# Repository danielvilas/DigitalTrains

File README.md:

# DigitalTrains
Digital Trains is a repository for storing and sharing my DCC/LCC setups

Up to Date this contians Circuits, boards and projects usefull for my model layout.
Each folder is a project I started. some are finished, others are Work In Progress

|Folder| Description|Status[^1]|
|:--|:--|:--|
|[ArduinoDCC++](ArduinoDCC++)|Board for use whit DCC++|Deprecated for DccBlocks
|[Breaker](Breaker)|DC breaker board, shorts protections|Frozen, no need on DCC[^2]|
|[dcc-turnout](dcc-turnout)|Board to control a turnout with servo| Alive - prototype phase|
|[dcc-turnout-config](dcc-turnout-config)|Tool to configure the dcc-turnout boards| Alive - conceptual design|
|[DccBlocks](DccBlocks)| Components to create a DCC system whit DCC++. Has subprojects| Stall - currently works, needs update to DCC++EX|
|[docs](docs)| Different documents may be usefull| Alive - Slow|
|[Esp32Lcc](Esp32Lcc)| Use an ESP32 as node for LCC| Stall - Reading about|
|[Interfaces](Interfaces)| Reference Designs to add conectivity| Done - until new needs|
|[kibot](kibot)| Yaml Config for kibot scripts..| Done - until new needs|
|[Libs](Libs)| KiCad Libraries| WIP |
|[MimicPanel](MimicPanel)| Hardware and software to create Mimic Panels| WIP|
|[pcbdraw](pcbdraw)| PcbDraw Library| WIP|
|[STM32103_Devel](STM32103_Devel)|STM32F103 Custom board| Depecated for refenece repository|

[^1]: More info inside each project
[^2]: Let the central handle shorts :sunglasses:

## Versioning
First projects uses a folder per version system, easy to follow, easy to view older versions, but mess the file system.

Current system based on tags, and the creation of doc directories with PDFs of the schematic and the layers.
## Tags of projects
* __db_dt_VERSION__ -> DccBlocks/Detection
* __dt_VERSION__ -> DccTurnout
* __dt_ms_VERSION__ -> DccTurnout/Modules/ServoPmosModule
* __db_abc_stop_VERSION__ -> DccBlocks/ABC/AbcStop
* __db_pd_VERSION__ ->  DccBlocks/DccPowerDistribution
* __i_lb_esp32_VERSION__ -> Interfaces/LocoBufferEsp32/board/LocoBufferEsp32
* __i_lb_esp32_c_VERSION__ -> Interfaces/LocoBufferEsp32/board/LocoBufferEsp32Craddle

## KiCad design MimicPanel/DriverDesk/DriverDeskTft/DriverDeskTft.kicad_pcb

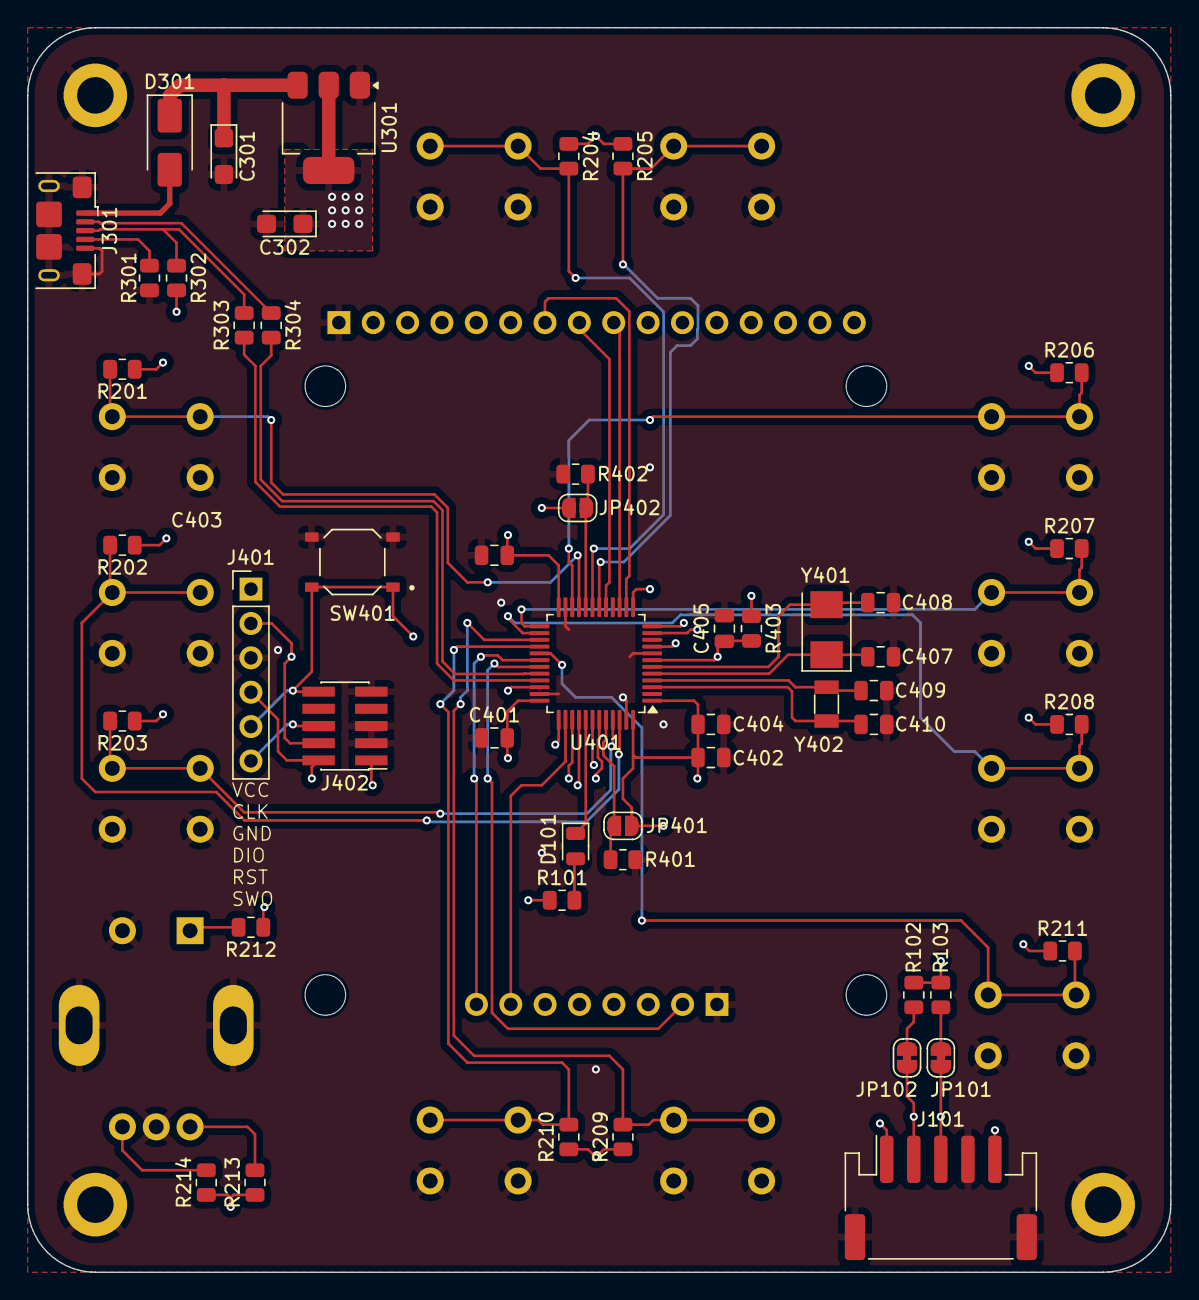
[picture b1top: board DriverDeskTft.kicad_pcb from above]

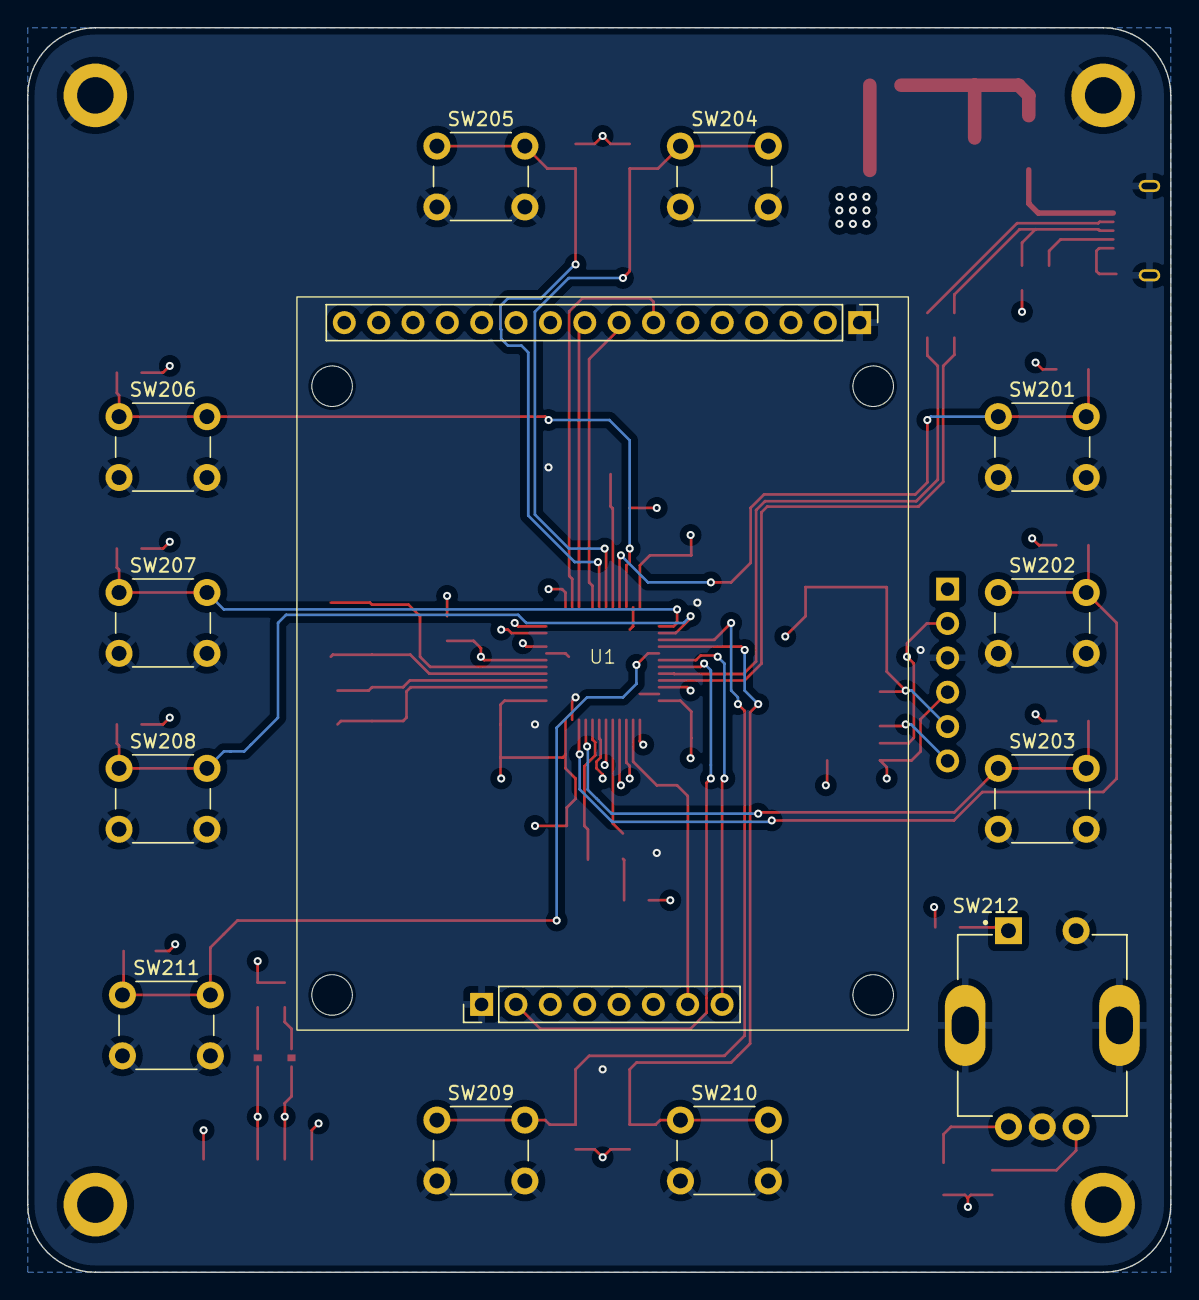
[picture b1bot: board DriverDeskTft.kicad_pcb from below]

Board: 4 copper layers, 84.5 x 92.0 mm, 67 parts (13 on the bottom side), 46 nets.

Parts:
C301, C302: 10uF; CP_EIA-3216-18_Kemet-A
C401, C402, C403, C404, C405: 100nf; C_0805_2012Metric
C407, C408: 20pf; C_0805_2012Metric
C409, C410: 10pf; C_0805_2012Metric
D101: LED; LED_0805_2012Metric
D301: ss14; D_SMA
H1, H2, H3, H4: MountingHole_Pad; MountingHole_2.7mm_M2.5_DIN965_Pad
J101: S5B-PH-SM4-TB; JST_PH_S5B-PH-SM4-TB_1x05-1MP_P2.00mm_Horizontal
J301: USB_B_Micro; USB_Micro-B_Amphenol_10118193-0001LF_Horizontal
J401: Conn_01x06_P1.27; PinHeader_1x06_P2.54mm_Vertical
J402: Conn_02x05 Odd_Even; PinHeader_2x05_P1.27mm_Vertical_SMD
JP101, JP102: SolderJumper_2_Bridged; SolderJumper-2_P1.3mm_Bridged_RoundedPad1.0x1.5mm
JP401, JP402: SolderJumper_2_Open; SolderJumper-2_P1.3mm_Open_RoundedPad1.0x1.5mm
R101: 1K; R_0805_2012Metric
R102, R103, R201, R202, R203, R204, R205, R206, R207, R208, R209, R210, R211, R212, R213, R214, R401, R402, R403: 10K; R_0805_2012Metric
R301: 100K; R_0805_2012Metric
R302: 1K5; R_0805_2012Metric
R303, R304: 20; R_0805_2012Metric
SW201, SW202, SW203, SW204, SW205, SW206, SW207, SW208, SW209, SW210, SW211: SW_Push; SW_PUSH_6mm_H5mm
SW212: RotaryEncoder_Switch; XDCR_PEC11R-4215F-S0024
SW401: PTS526; SW_PTS526_SM08_SMTR2_LFS
U1: TFT 1.8 SPI
U301: AMS1117-3.3; SOT-223-3_TabPin2
U401: STM32F103CBTx; LQFP-48_7x7mm_P0.5mm
Y401: 8MHz; Crystal_SMD_5032-2Pin_5.0x3.2mm
Y402: 32.768kHz; Crystal_SMD_3215-2Pin_3.2x1.5mm

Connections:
+5V: C301.1, D301.1 (K), U301.3 (VI)
/BTN_1: R201.2, SW201.1, U401.21 (PB10)
/BTN_2: R202.2, SW202.1, U401.46 (PB9)
/BTN_3: R203.2, SW203.1, U401.45 (PB8)
/BTN_4: R204.2, SW204.1, U401.19 (PB1)
/BTN_5: R205.2, SW205.1, U401.18 (PB0)
/BTN_6: R206.2, SW206.1, U401.22 (PB11)
/BTN_7: R207.2, SW207.1, U401.25 (PB12)
/BTN_8: R208.2, SW208.1, U401.26 (PB13)
/BTN_9: R209.2, SW209.1, U401.27 (PB14)
/BTN_10: R210.2, SW210.1, U401.28 (PB15)
/I2C_INT: J101.5, U401.40 (PB4)
/I2C_SCL: J101.3, JP101.1 (A), U401.42 (PB6)
/I2C_SDA: J101.2, JP102.1 (A), U401.43 (PB7)
/LED: D101.1 (K), U401.41 (PB5)
/RENC_A: R213.2, SW212.A, U401.11 (PA1)
/RENC_B: R214.2, SW212.B, U401.12 (PA2)
/RENC_H: R211.2, SW211.1, U401.29 (PA8)
/RENC_S: R212.2, SW212.S1, U401.13 (PA3)
/STM32F103/BOOT0: JP401.1 (A), R401.1, U401.44 (BOOT0)
/STM32F103/BOOT1: JP402.1 (A), R402.1, U401.20 (PB2)
/STM32F103/NRST: C405.1, J401.5, J402.10, R403.2, SW401.1, U401.7 (NRST)
/STM32F103/OSC32_IN: C409.1, U401.4 (PC15), Y402.1
/STM32F103/OSC32_OUT: C410.1, U401.3 (PC14), Y402.2
/STM32F103/OSC_IN: C407.1, U401.5 (PD0), Y401.1
/STM32F103/OSC_OUT: C408.1, U401.6 (PD1), Y401.2
/STM32F103/PA13: J401.4, J402.2, U401.34 (PA13)
/STM32F103/PA14: J401.2, J402.4, U401.37 (PA14)
/STM32F103/PB3: J401.6, J402.6, U401.39 (PB3)
/TFT_BL: U1.18 (BL), U401.31 (PA10)
/TFT_CLK: U1.9 (SCL), U401.15 (PA5)
/TFT_CS: U1.23 (CS), U401.38 (PA15)
/TFT_DC: U1.7 (RS), U401.14 (PA4)
/TFT_DIN: U1.8 (SDA), U401.17 (PA7)
/TFT_RST: U1.24 (RST), U401.30 (PA9)
/USB/USB_N: J301.2 (D-), R304.1
/USB/USB_P: J301.3 (D+), R302.1, R303.2
/USB/VCC_USB: D301.2 (A), J301.1 (VBUS)
/USB_DN: R304.2, U401.32 (PA11)
/USB_DP: R303.1, U401.33 (PA12)
GND: C301.2, C302.2, C401.1, C402.1, C403.1, C404.1, C405.2, C407.2, C408.2, C409.2, C410.2, H1.1, H2.1, H3.1, H4.1, J101.4, J101.MP (MountPin), J301.5 (GND), J301.6 (Shield), J401.3, J402.3, J402.5, J402.9, R301.2, R401.2, R402.2, SW201.2, SW202.2, SW203.2, SW204.2, SW205.2, SW206.2, SW207.2, SW208.2, SW209.2, SW210.2, SW211.2, SW212.C, SW212.MP, SW212.S2, SW401.2, U1.1 (GND), U1.17 (GND), U301.1 (GND), U401.8 (VSSA), U401.23 (VSS), U401.35 (VSS), U401.47 (VSS)
unnamed: D101.2 (A), R101.2
unnamed: J301.4 (ID), R301.1
unnamed: JP101.2 (B), R103.2
unnamed: JP102.2 (B), R102.2
VCC: C302.1, C401.2, C402.2, C403.2, C404.2, J101.1, J401.1, J402.1, JP401.2 (B), JP402.2 (B), R101.1, R102.1, R103.1, R201.1, R202.1, R203.1, R204.1, R205.1, R206.1, R207.1, R208.1, R209.1, R210.1, R211.1, R212.1, R213.1, R214.1, R302.2, R403.1, U1.2 (VCC), U1.19 (VCC), U301.2 (VO), U401.1 (VBAT), U401.9 (VDDA), U401.24 (VDD), U401.36 (VDD), U401.48 (VDD)

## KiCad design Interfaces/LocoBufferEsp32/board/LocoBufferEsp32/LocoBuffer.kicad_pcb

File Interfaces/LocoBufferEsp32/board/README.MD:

# LocoBuffer from LocoLinx32U4

Board for use wiht the [https://github.com/mrrwa/LocoNet/tree/master/examples/LocoLinx32U4] code, there is a copy on this repository for platform.io .

# 0.0.1
- [x] USB
- [x] Loconet
- [x] Leds loconet
- [x] ESP32
- [ ] Btn Reset

# 0.0.X
- [] Loconet Power 
- [] Loconet Master
- [] USB-C
- [] Non-Inv TX
- [] SD
- [] BTN AP
- [] Led Wifi RGB

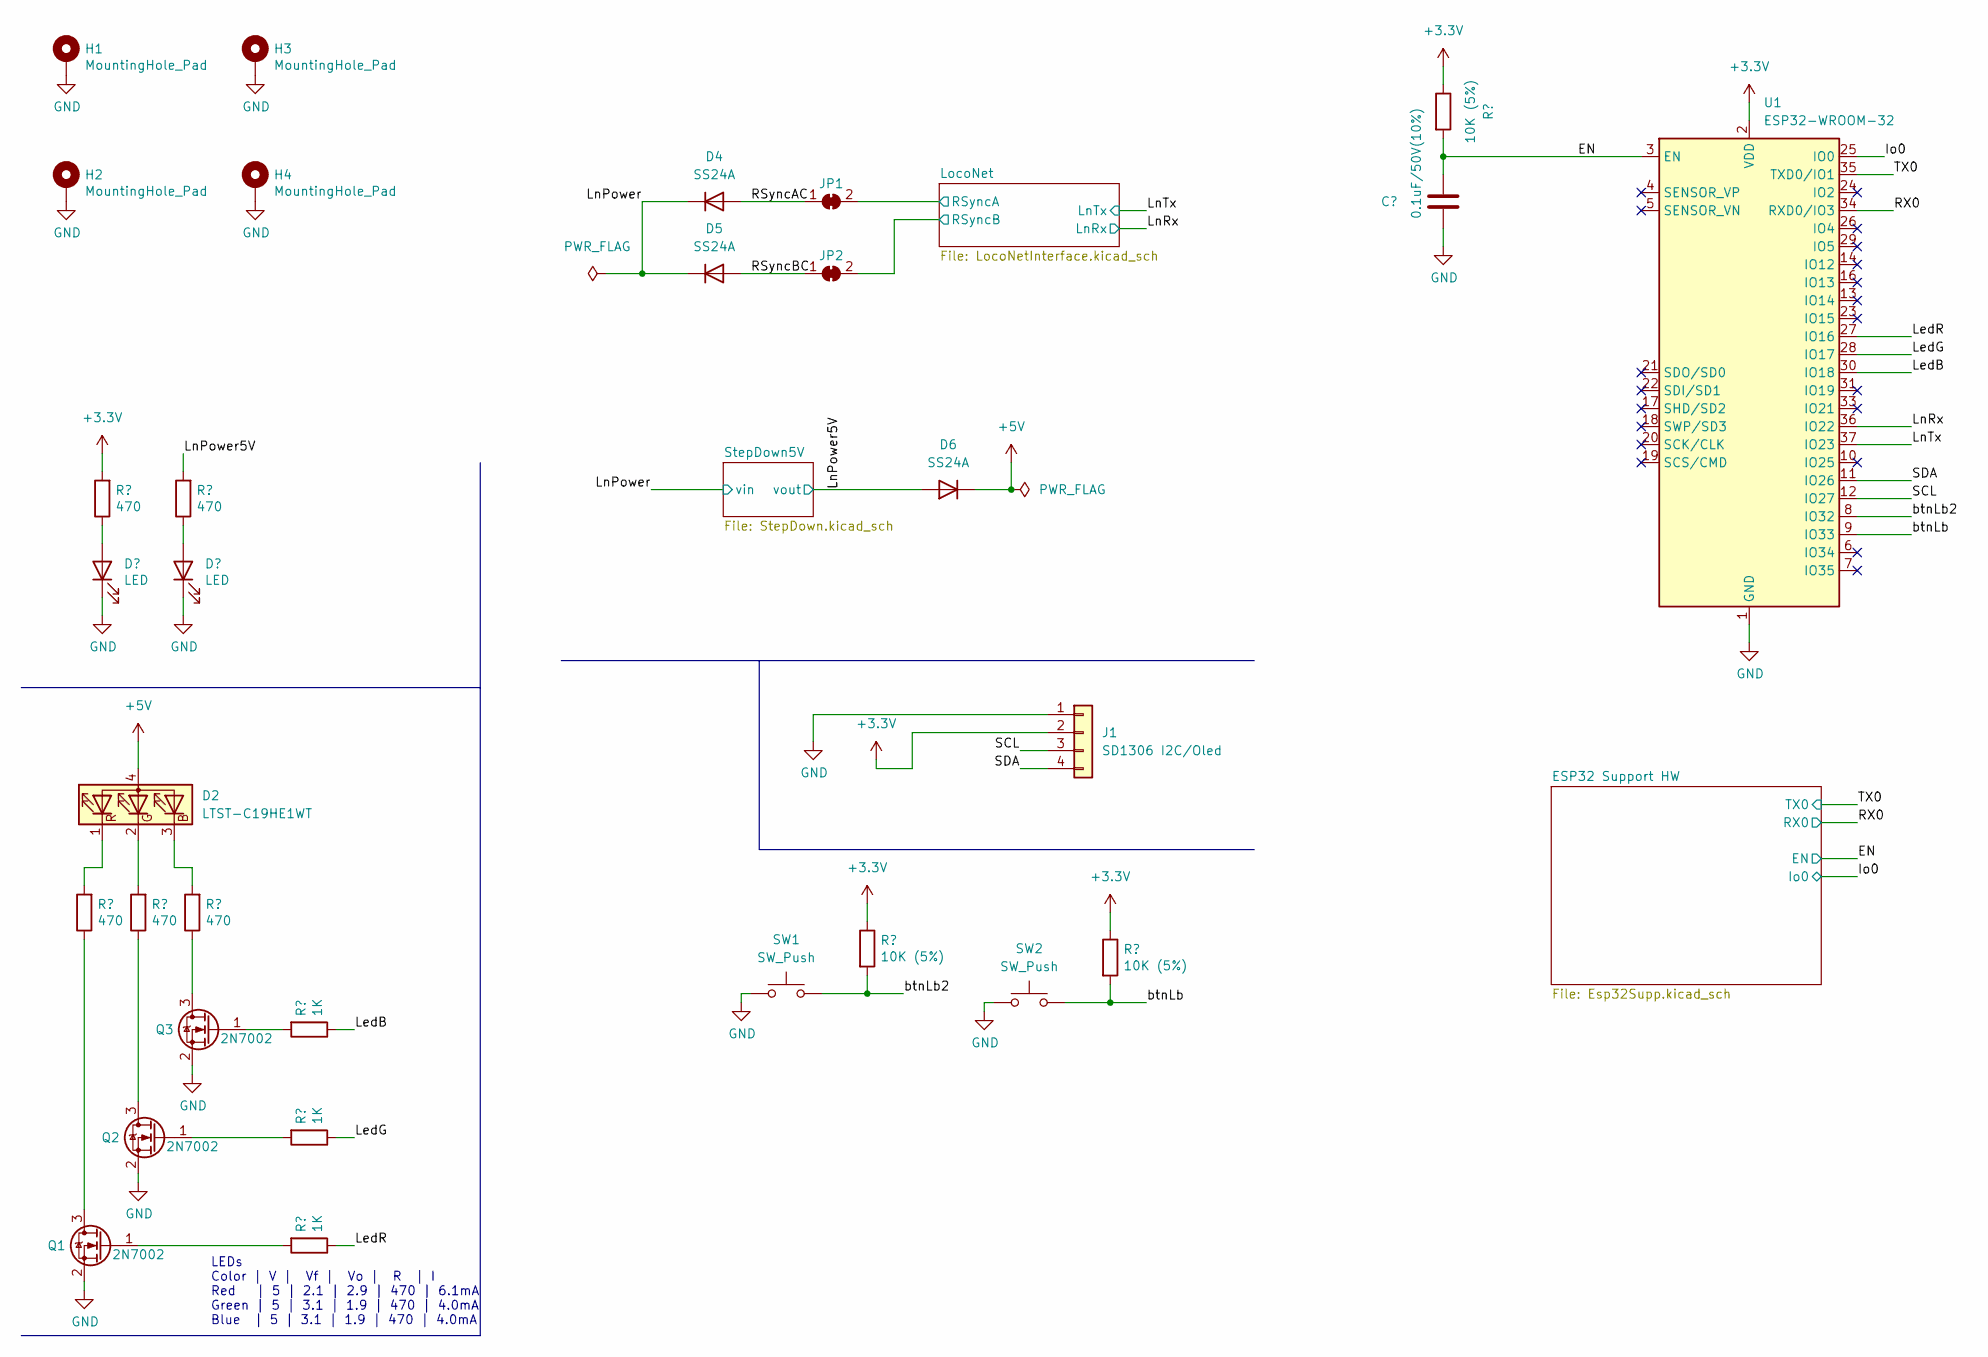
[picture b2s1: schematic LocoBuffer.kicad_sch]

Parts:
C1: 0.1uF/50V(10%); C_0805_2012Metric; LCSC C49678
D1, D3: LED; LED_0805_2012Metric; LCSC C2296
D2: LTST-C19HE1WT; LED_LiteOn_LTST-C19HE1WT; LCSC C458749
D4, D5, D6: SS24A; D_SMA; LCSC C95872
H1, H2, H3, H4: MountingHole_Pad; MountingHole_3.2mm_M3_ISO7380_Pad
J1: SD1306 I2C/Oled; 128x64OLED
JP1, JP2: SolderJumper_2_Bridged; SolderJumper-2_P1.3mm_Bridged2Bar_RoundedPad1.0x1.5mm
Q1, Q2, Q3: 2N7002; SOT-23; LCSC C8545
R1, R2, R3, R4, R5: 470; R_0805_2012Metric; LCSC C17710
R6, R7, R8: 1K; R_0805_2012Metric; LCSC C17513
R9, R10, R11: 10K (5%); R_0805_2012Metric; LCSC C17414
SW1, SW2: SW_Push; SW_SPST_CK_RS282G05A3
U1: ESP32-WROOM-32; LCSC C701343

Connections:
+3.3V: J1.2, R2.2, R9.1, R10.1, R11.1, U1.2 (VDD); also elsewhere on the board
+5V: D2.4 (A), D6.1 (K); also elsewhere on the board
/EN: C1.1, R11.2, U1.3 (EN); also elsewhere on the board
/Io0: U1.25 (IO0); also elsewhere on the board
/LedB: R6.1, U1.30 (IO18)
/LedG: R7.1, U1.28 (IO17)
/LedR: R8.1, U1.27 (IO16)
/LnPower: D4.1 (K), D5.1 (K); also elsewhere on the board
/LnPower5V: D6.2 (A), R4.2; also elsewhere on the board
/LnRx: U1.36 (IO22); also elsewhere on the board
/LnTx: U1.37 (IO23); also elsewhere on the board
/LocoNet/RSyncA: JP1.2 (B); also elsewhere on the board
/LocoNet/RSyncB: JP2.2 (B); also elsewhere on the board
/RSyncAC: D4.2 (A), JP1.1 (A)
/RSyncBC: D5.2 (A), JP2.1 (A)
/RX0: U1.34 (RXD0/IO3); also elsewhere on the board
/SCL: J1.3, U1.12 (IO27)
/SDA: J1.4, U1.11 (IO26)
/TX0: U1.35 (TXD0/IO1); also elsewhere on the board
/btnLb: R10.2, SW2.2, U1.9 (IO33)
/btnLb2: R9.2, SW1.2, U1.8 (IO32)
GND: C1.2, D1.1 (K), D3.1 (K), H1.1, H2.1, H3.1, H4.1, J1.1, Q1.2 (S), Q2.2 (S), Q3.2 (S), SW1.1, SW2.1, U1.1 (GND), U1.15 (GND), U1.38 (GND), U1.39 (GND); also elsewhere on the board
unnamed: D1.2 (A), R2.1
unnamed: D2.3 (BK), R5.2
unnamed: D2.2 (GK), R3.2
unnamed: D2.1 (RK), R1.2
unnamed: D3.2 (A), R4.1
unnamed: Q1.3 (D), R1.1
unnamed: Q1.1 (G), R8.2
unnamed: Q2.3 (D), R3.1
unnamed: Q2.1 (G), R7.2
unnamed: Q3.3 (D), R5.1
unnamed: Q3.1 (G), R6.2

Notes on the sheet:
LEDs Color | V | Vf | Vo | R | I Red | 5 | 2.1 | 2.9 | 470 | 6.1mA Green | 5 | 3.1 | 1.9 | 470 | 4.0mA Blue | 5 | 3.1 | 1.9 | 470 | 4.0mA

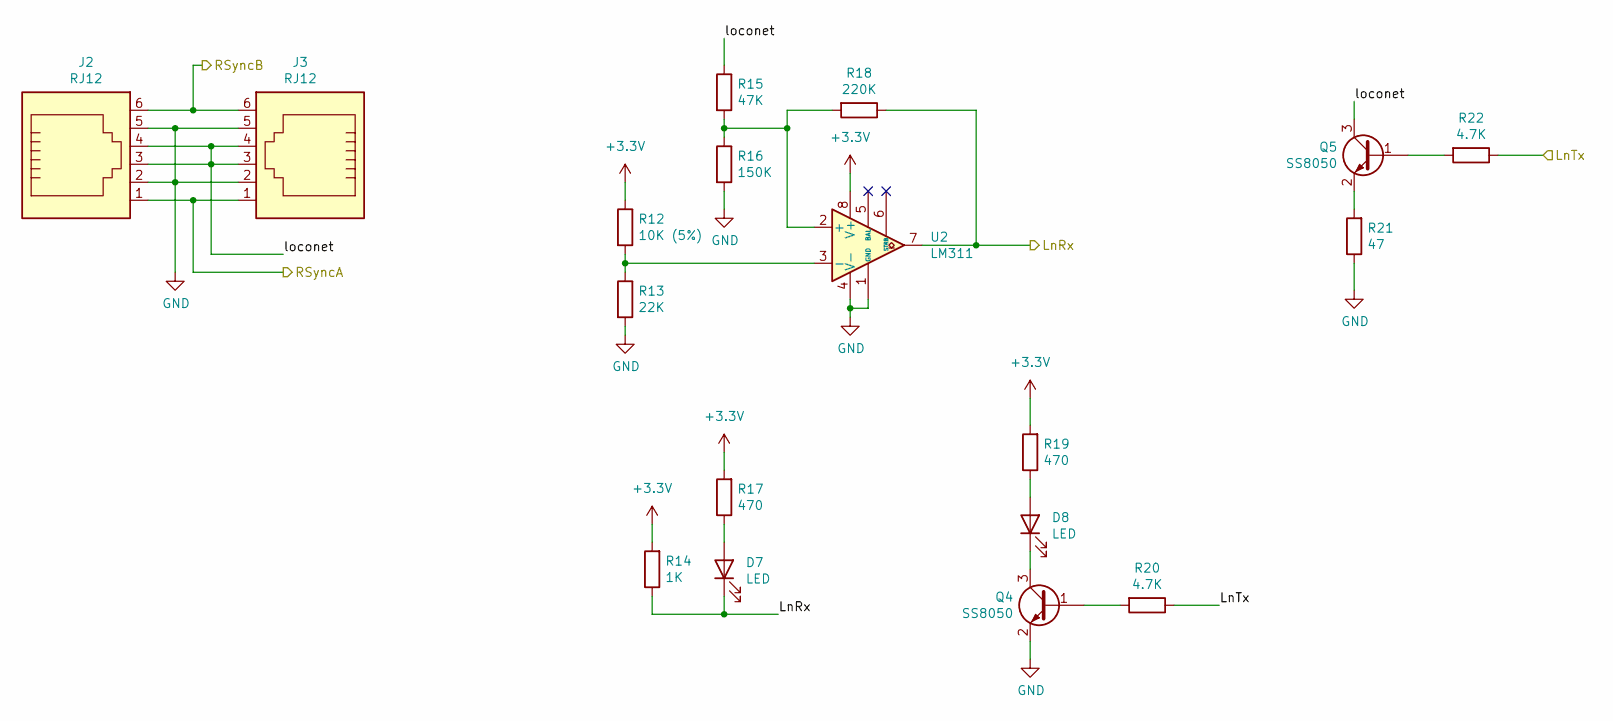
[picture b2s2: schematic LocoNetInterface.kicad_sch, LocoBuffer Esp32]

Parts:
D7, D8: LED; LED_0805_2012Metric; LCSC C2296
J2, J3: RJ12; AMPHENOL_RJE0166001
Q4, Q5: SS8050; SOT-23; LCSC C2150
R12: 10K (5%); R_0805_2012Metric; LCSC C17414
R13: 22K; R_0805_2012Metric; LCSC C17560
R14: 1K; R_0805_2012Metric; LCSC C17513
R15: 47K; R_0805_2012Metric; LCSC C17713
R16: 150K; R_0805_2012Metric; LCSC C17470
R17, R19: 470; R_0805_2012Metric; LCSC C17710
R18: 220K; R_0805_2012Metric; LCSC C17556
R20, R22: 4.7K; R_0805_2012Metric; LCSC C229219
R21: 47; R_0805_2012Metric; LCSC C17714
U2: LM311; SOIC-8_3.9x4.9mm_P1.27mm; LCSC C12597

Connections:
+3.3V: R12.1, R14.2, R17.2, R19.2, U2.8 (V+); also elsewhere on the board
/LnRx: D7.1 (K), R14.1, R18.1, U2.7; also elsewhere on the board
/LnTx: R20.1, R22.1; also elsewhere on the board
/LocoNet/RSyncA: J2.1, J3.1; also elsewhere on the board
/LocoNet/RSyncB: J2.6, J3.6; also elsewhere on the board
/LocoNet/loconet: J2.3, J2.4, J3.3, J3.4, Q5.3 (C), R15.1
GND: J2.2, J2.5, J3.2, J3.5, Q4.2 (E), R13.2, R16.2, R21.1, U2.1 (GND), U2.4 (V-); also elsewhere on the board
unnamed: D7.2 (A), R17.1
unnamed: D8.2 (A), R19.1
unnamed: D8.1 (K), Q4.3 (C)
unnamed: Q4.1 (B), R20.2
unnamed: Q5.1 (B), R22.2
unnamed: Q5.2 (E), R21.2
unnamed: R15.2, R16.1, R18.2, U2.2 (+)
unnamed: R12.2, R13.1, U2.3 (-)

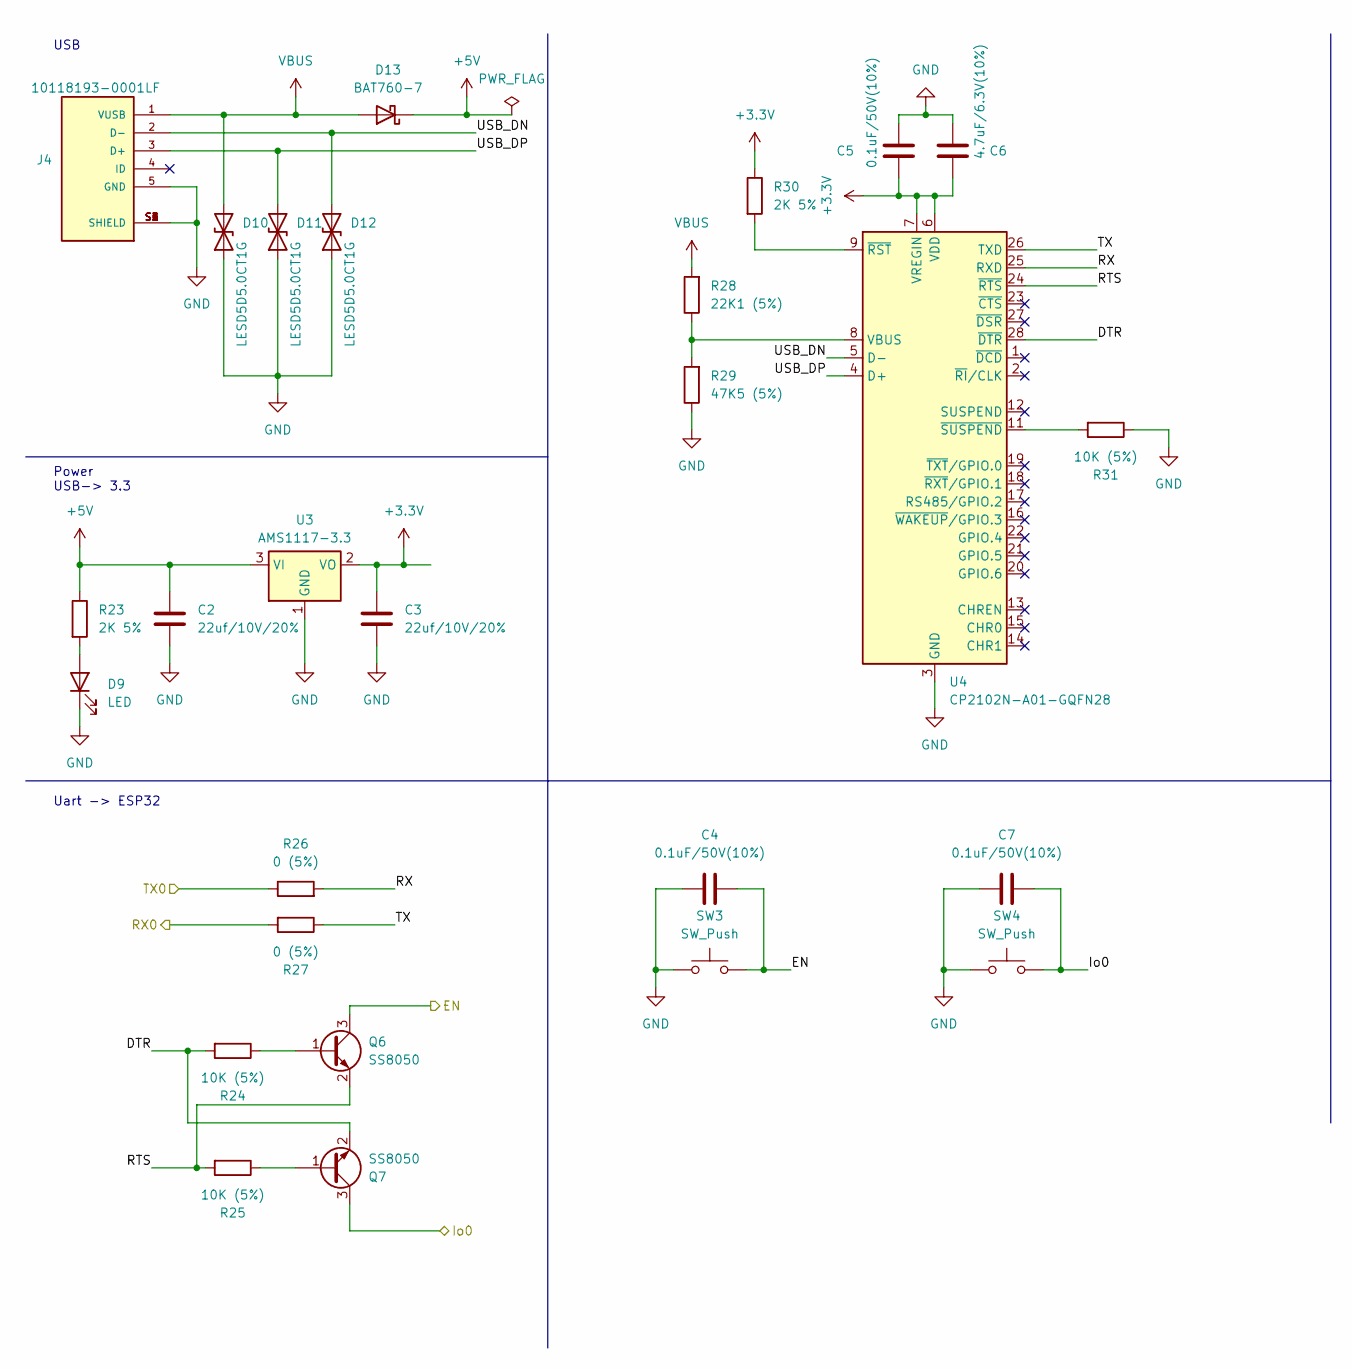
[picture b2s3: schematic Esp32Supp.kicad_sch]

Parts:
C2, C3: 22uf/10V/20%; C_0805_2012Metric; LCSC C45783
C4, C5, C7: 0.1uF/50V(10%); C_0805_2012Metric; LCSC C49678
C6: 4.7uF/6.3V(10%); C_0805_2012Metric; LCSC C1779
D9: LED; LED_0805_2012Metric; LCSC C2296
D10, D11, D12: LESD5D5.0CT1G; D_SOD-523; LCSC C383211
D13: BAT760-7; D_SOD-323; LCSC C124187
J4: 10118193-0001LF; AMPHENOL_10118193-0001LF; PARTREV E; LCSC C132562
Q6, Q7: SS8050; SOT-23; LCSC C2150
R23, R30: 2K 5%; R_0805_2012Metric; LCSC C212449
R24, R25, R31: 10K (5%); R_0805_2012Metric; LCSC C17414
R26, R27: 0 (5%); R_0805_2012Metric; LCSC C2936632
R28: 22K1 (5%); R_0805_2012Metric; LCSC C153391
R29: 47K5 (5%); R_0805_2012Metric; LCSC C245335
SW3, SW4: SW_Push; SW_SPST_CK_RS282G05A3
U3: AMS1117-3.3; SOT-223-3_TabPin2; LCSC C6186
U4: CP2102N-A01-GQFN28; QFN-28-1EP_5x5mm_P0.5mm_EP3.35x3.35mm; LCSC C964632

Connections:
+3.3V: C3.1, C5.2, C6.2, R30.1, U3.2 (VO), U4.6 (VDD), U4.7 (VREGIN); also elsewhere on the board
+5V: C2.1, D13.1 (K), R23.1, U3.3 (VI); also elsewhere on the board
/EN: C4.2, Q6.3 (C), SW3.2; also elsewhere on the board
/ESP32 Support HW/DTR: Q7.2 (E), R24.2, U4.28 (~DTR)
/ESP32 Support HW/RTS: Q6.2 (E), R25.2, U4.24 (~RTS)
/ESP32 Support HW/RX: R26.2, U4.25 (RXD)
/ESP32 Support HW/TX: R27.1, U4.26 (TXD)
/ESP32 Support HW/USB_DN: D12.2 (A2), J4.2 (D-), U4.5 (D-)
/ESP32 Support HW/USB_DP: D11.2 (A2), J4.3 (D+), U4.4 (D+)
/Io0: C7.2, Q7.3 (C), SW4.2; also elsewhere on the board
/RX0: R27.2; also elsewhere on the board
/TX0: R26.1; also elsewhere on the board
GND: C2.2, C3.2, C4.1, C5.1, C6.1, C7.1, D9.1 (K), D10.1 (A1), D11.1 (A1), D12.1 (A1), J4.5 (GND), J4.S1 (SHIELD), J4.S2 (SHIELD), J4.S3 (SHIELD), J4.S4 (SHIELD), J4.S5 (SHIELD), J4.S6 (SHIELD), R29.1, R31.1, SW3.1, SW4.1, U3.1 (GND), U4.3 (GND), U4.29 (GND); also elsewhere on the board
unnamed: D9.2 (A), R23.2
unnamed: Q6.1 (B), R24.1
unnamed: Q7.1 (B), R25.1
unnamed: R28.1, R29.2, U4.8 (VBUS)
unnamed: R30.2, U4.9 (~RST)
unnamed: R31.2, U4.11 (~SUSPEND)
VBUS: D10.2 (A2), D13.2 (A), J4.1 (VUSB), R28.2

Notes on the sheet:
Power USB-> 3.3
Uart -> ESP32
USB

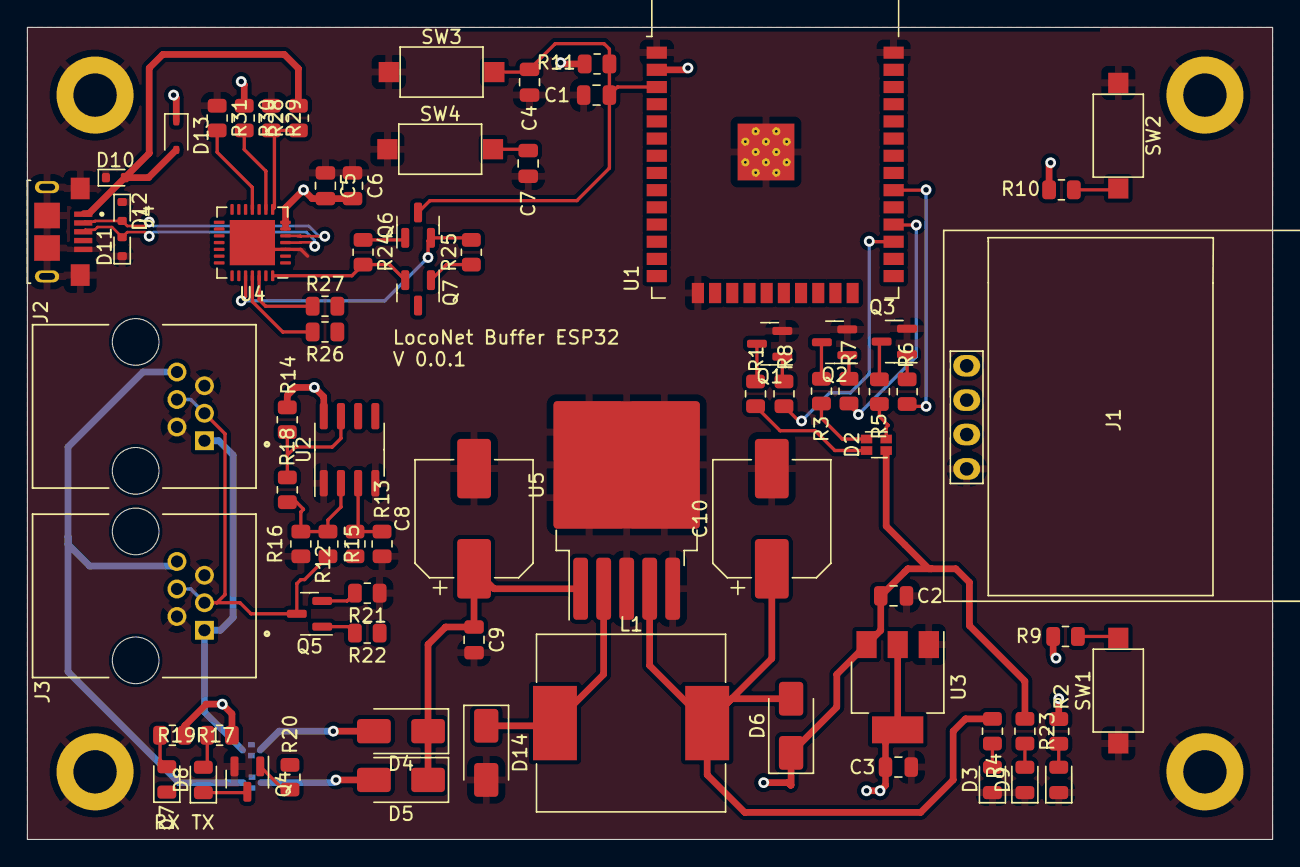
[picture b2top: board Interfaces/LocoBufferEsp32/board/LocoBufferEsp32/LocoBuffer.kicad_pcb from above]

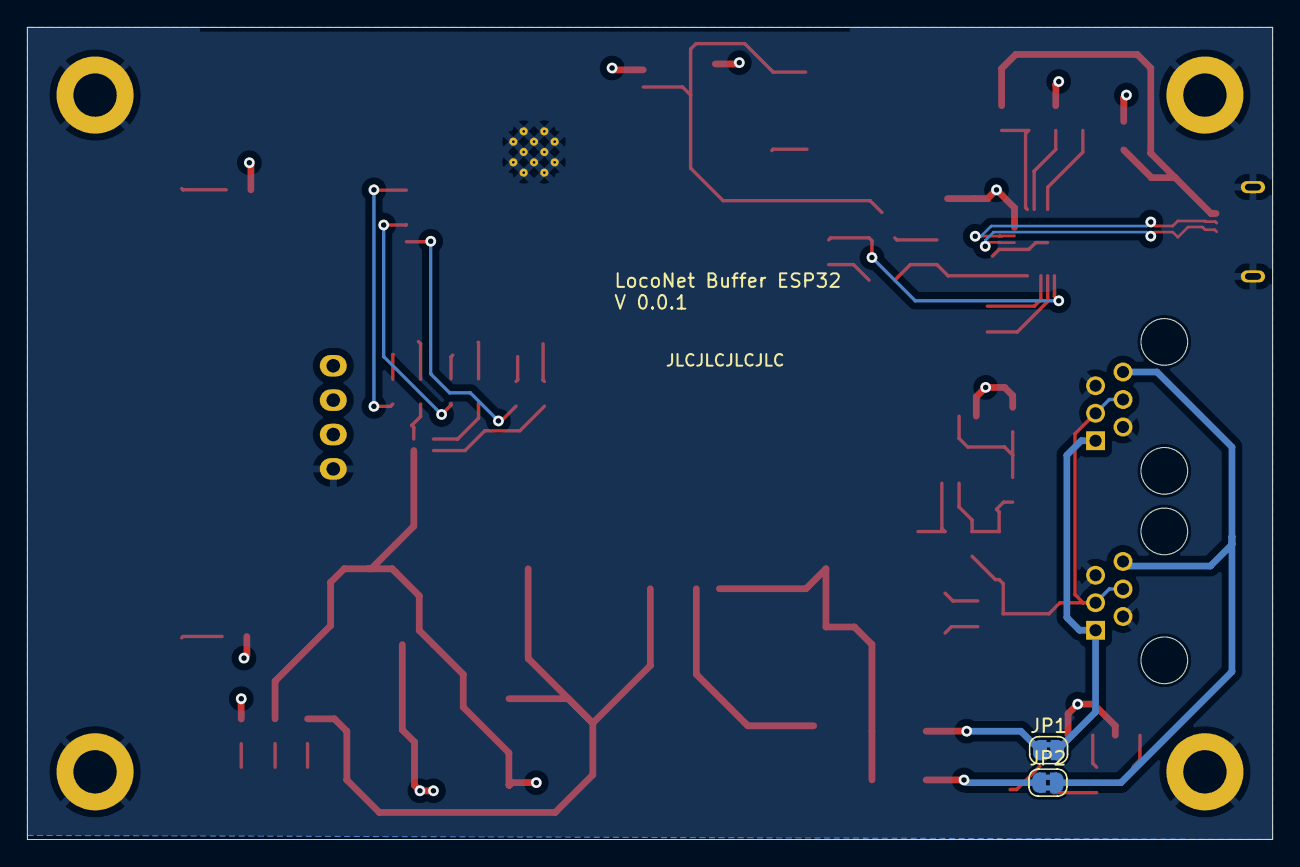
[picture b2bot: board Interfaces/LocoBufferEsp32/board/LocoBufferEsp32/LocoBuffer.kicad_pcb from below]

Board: 4 copper layers, 92.0 x 60.0 mm, 82 parts (2 on the bottom side), 56 nets.

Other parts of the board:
C8: 220uF; CP_Elec_8x10.5
C9: 100nf; C_0805_2012Metric
C10: 220uf; CP_Elec_8x10.5
D14: B330A; D_SMA
L1: 100uH; L_Sunlord_MWSA1206S-101
U5: LM2576S-5; TO-263-5_TabPin3

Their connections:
/LnPower: C8.1, C9.1, U5.1 (VIN); also elsewhere on the board
/LnPower5V: C10.1, L1.2, U5.4 (FB); also elsewhere on the board
GND: C8.2, C9.2, C10.2, D14.2 (A), U5.3 (GND), U5.5 (~ON/OFF); also elsewhere on the board
unnamed: D14.1 (K), L1.1, U5.2 (OUT)

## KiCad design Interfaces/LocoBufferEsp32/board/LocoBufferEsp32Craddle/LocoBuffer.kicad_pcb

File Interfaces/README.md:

# Interfaces to access a DCC/LCB system
Different circuits/boards to access to DCC systems or Layout Control Bus.

## Subprojects
* __[DCC](DCC)__: DCC -> TTL Isolated Module
* __[LocoBuffer](LocoBuffer)__: USB -> Loconet Interface
* __[LocoBufferEsp32](LocoBufferEsp32)__: Loconet-> ESP32 -> wifi Interface
* __[LocoNet](LocoNet)__: LocoNet -> TTL

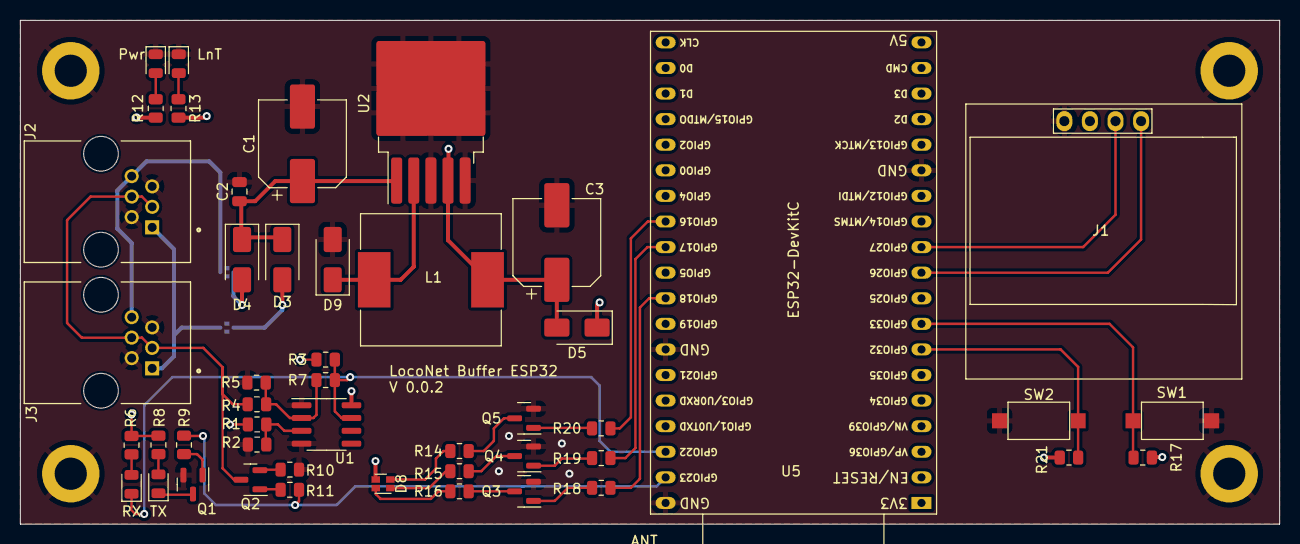
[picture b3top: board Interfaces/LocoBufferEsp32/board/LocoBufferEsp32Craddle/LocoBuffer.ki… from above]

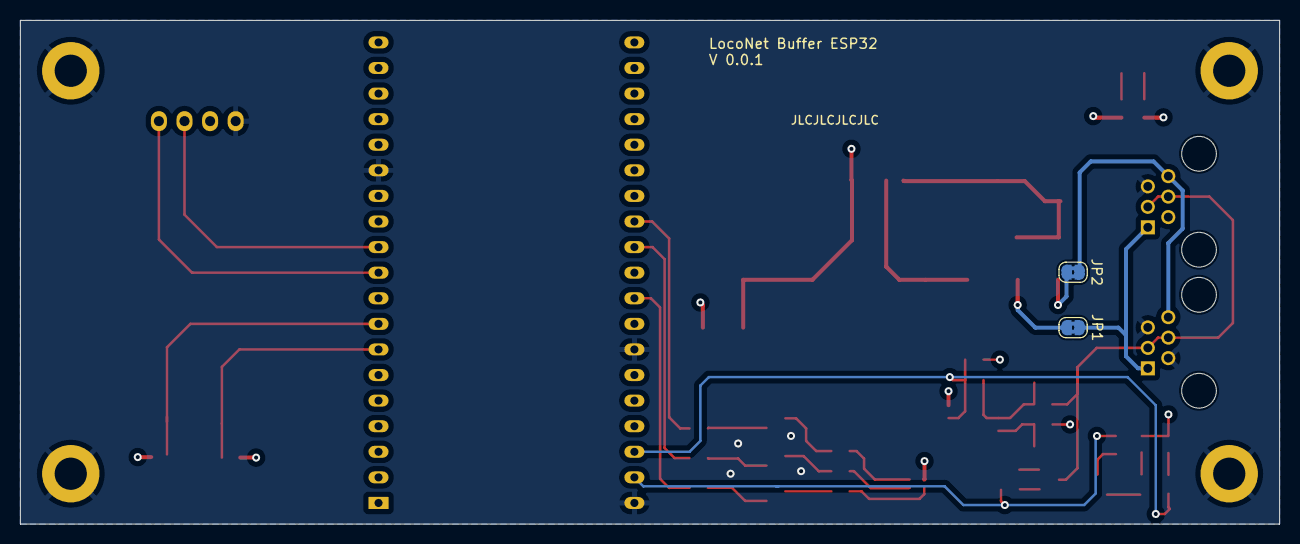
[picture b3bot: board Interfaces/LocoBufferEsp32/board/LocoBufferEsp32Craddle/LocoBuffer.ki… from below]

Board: 4 copper layers, 125.0 x 50.0 mm, 53 parts (2 on the bottom side), 39 nets.

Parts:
C1: 220uF; CP_Elec_8x10.5
C2: 100nf; C_0805_2012Metric
C3: 220uf; CP_Elec_8x10.5
D1, D2, D6, D7: LED; LED_0805_2012Metric
D3, D4, D5: SS24A; D_SMA
D8: LTST-C19HE1WT; LED_LiteOn_LTST-C19HE1WT
D9: B330A; D_SMA
H1, H2, H3, H4: MountingHole_Pad; MountingHole_3.2mm_M3_ISO7380_Pad
J1: SD1306 I2C/Oled; 128x64OLED
J2, J3: RJ12; AMPHENOL_RJE0166001
JP1, JP2: SolderJumper_2_Bridged; SolderJumper-2_P1.3mm_Bridged2Bar_RoundedPad1.0x1.5mm
L1: 100uH; L_Sunlord_MWSA1206S-101
Q1, Q2: SS8050; SOT-23
Q3, Q4, Q5: 2N7002; SOT-23
R1, R17, R21: 10K (5%); R_0805_2012Metric
R2: 22K; R_0805_2012Metric
R3, R18, R19, R20: 1K; R_0805_2012Metric
R4: 47K; R_0805_2012Metric
R5: 150K; R_0805_2012Metric
R6, R8, R12, R13, R14, R15, R16: 470; R_0805_2012Metric
R7: 220K; R_0805_2012Metric
R9, R11: 4.7K; R_0805_2012Metric
R10: 47; R_0805_2012Metric
SW1, SW2: SW_Push; SW_SPST_CK_RS282G05A3
U1: LM311; SOIC-8_3.9x4.9mm_P1.27mm
U2: LM2576S-5; TO-263-5_TabPin3
U5: ESP32-DevKitC

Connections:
+3.3V: J1.2, R1.1, R3.2, R6.2, R8.2, R12.2, R17.1, R21.1, U1.8 (V+), U5.1 (3V3)
+5V: D5.1 (K), D8.4 (A), U5.19 (5V)
/LedB: R18.1, U5.30 (GPIO18)
/LedG: R19.1, U5.28 (GPIO17)
/LedR: R20.1, U5.27 (GPIO16)
/LnPower: C1.1, C2.1, D3.1 (K), D4.1 (K), U2.1 (VIN)
/LnPower5V: C3.1, D5.2 (A), L1.2, R13.2, U2.4 (FB)
/LnRx: D1.1 (K), R3.1, R7.1, U1.7, U5.36 (GPIO22)
/LnTx: R9.1, R11.1, U5.37 (GPIO23)
/LocoNet/RSyncA: J2.1, J3.1, JP1.2 (B)
/LocoNet/RSyncB: J2.6, J3.6, JP2.2 (B)
/LocoNet/loconet: J2.3, J2.4, J3.3, J3.4, Q2.3 (C), R4.1
/RSyncAC: D3.2 (A), JP1.1 (A)
/RSyncBC: D4.2 (A), JP2.1 (A)
/SCL: J1.3, U5.11 (ADC2_CH7/GPIO27)
/SDA: J1.4, U5.10 (DAC_2/ADC2_CH9/GPIO26)
/btnLb: R17.2, SW1.2, U5.8 (32K_XN/GPIO33/ADC1_CH5)
/btnLb2: R21.2, SW2.2, U5.7 (32K_XP/GPIO32/ADC1_CH4)
GND: C1.2, C2.2, C3.2, D6.1 (K), D7.1 (K), D9.2 (A), H1.1, H2.1, H3.1, H4.1, J1.1, J2.2, J2.5, J3.2, J3.5, Q1.2 (E), Q3.2 (S), Q4.2 (S), Q5.2 (S), R2.2, R5.2, R10.1, SW1.1, SW2.1, U1.1 (GND), U1.4 (V-), U2.3 (GND), U2.5 (~ON/OFF), U5.14 (GND), U5.32 (GND), U5.38 (GND)
unnamed: D1.2 (A), R6.1
unnamed: D2.2 (A), R8.1
unnamed: D2.1 (K), Q1.3 (C)
unnamed: D6.2 (A), R12.1
unnamed: D7.2 (A), R13.1
unnamed: D8.3 (BK), R16.2
unnamed: D8.2 (GK), R15.2
unnamed: D8.1 (RK), R14.2
unnamed: D9.1 (K), L1.1, U2.2 (OUT)
unnamed: Q1.1 (B), R9.2
unnamed: Q2.1 (B), R11.2
unnamed: Q2.2 (E), R10.2
unnamed: Q3.3 (D), R16.1
unnamed: Q3.1 (G), R18.2
unnamed: Q4.3 (D), R15.1
unnamed: Q4.1 (G), R19.2
unnamed: Q5.3 (D), R14.1
unnamed: Q5.1 (G), R20.2
unnamed: R4.2, R5.1, R7.2, U1.2 (+)
unnamed: R1.2, R2.1, U1.3 (-)

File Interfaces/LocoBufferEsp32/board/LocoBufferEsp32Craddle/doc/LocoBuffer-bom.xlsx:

|  | Bill of Materials
 |  | Schematic: | LocoBuffer | Component Groups: | 24
 |  | Variant: | default | Component Count: | 47 (43 SMD/ 4 THT)
 |  | Revision: | 0.0.1 | Fitted Components: | 47 (43 SMD/ 4 THT)
 |  | Date: | 2023-07-17 | Number of PCBs: | 1
 |  | KiCad Version: | 7.0.5.1-1-g8f565ef7f0-dirty-deb11 | Total Components: | 47
Row | Description | Part | References | Value | Footprint | Quantity Per PCB | Status | Datasheet | LCSC | Sim.Device | Sim.Pins
1 | Unpolarized capacitor | C | C2 | 100nf | C_0805_2012Metric | 1 |  | ~ | C282732
2 | Polarized capacitor | C_Polarized | C1 C3 | 220uF | CP_Elec_8x10.5 | 2 |  | ~ | C131124
3 | 30V 3A Schottky Barrier Rectifier Diode, SMC | B330 | D9 | B330A | D_SMA | 1 |  | http://www.jameco.com/Jameco/Products/ProdDS/1538777.pdf | C110485
4 | Light emitting diode | LED | D1 D2 D6 D7 | LED | LED_0805_2012Metric | 4 |  | ~ | C2296
5 | RGB LED, red/green/blue/anode | LED_RGBA | D8 | LTST-C19HE1WT | LED_LiteOn_LTST-C19HE1WT | 1 |  | ~ | C458749
6 | Diode | D | D3 D4 D5 | SS24A | D_SMA | 3 |  | ~ | C95872 | D | 1=K 2=A
7 | RJ connector, 6P6C (6 positions 6 connected) | RJ12 | J2 J3 | RJ12 | AMPHENOL_RJE0166001 | 2 |  | ~
8 | Generic connector, single row, 01x04, script generated (kicad-library-utils/sch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 | Conn_01x04 | J1 | SD1306 I2C/Oled | 128x64OLED | 1 |  | ~
9 | Inductor | L | L1 | 100uH | L_Sunlord_MWSA1206S-101 | 1 |  | ~ | C408533
10 | 0.115A Id, 60V Vds, N-Channel MOSFET, SOT-23 | 2N7002 | Q3 Q4 Q5 | 2N7002 | SOT-23 | 3 |  | https://www.onsemi.com/pub/Collateral/NDS7002A-D.PDF | C8545
11 | NPN transistor, base/emitter/collector | Q_NPN_BEC | Q1 Q2 | SS8050 | SOT-23 | 2 |  | ~ | C2150
12 | Resistor | R | R10 | 47 | R_0805_2012Metric | 1 |  | ~ | C17714
13 | Resistor | R | R6 R8 R12 R13 R14 R15 R16 | 470 | R_0805_2012Metric | 7 |  | ~ | C17710
14 | Resistor | R | R3 R18 R19 R20 | 1K | R_0805_2012Metric | 4 |  | ~ | C17513
15 | Resistor | R | R9 R11 | 4.7K | R_0805_2012Metric | 2 |  | ~ | C229219
16 | Resistor | R | R2 | 22K | R_0805_2012Metric | 1 |  | ~ | C17560
17 | Resistor | R | R4 | 47K | R_0805_2012Metric | 1 |  | ~ | C17713
18 | Resistor | R | R5 | 150K | R_0805_2012Metric | 1 |  | ~ | C17470
19 | Resistor | R | R7 | 220K | R_0805_2012Metric | 1 |  | ~ | C17556
20 | Resistor | R | R1 R17 R21 | 10K (5%) | R_0805_2012Metric | 3 |  | ~ | C17414
21 | Push button switch, generic, two pins | SW_Push | SW1 SW2 | SW_Push | SW_SPST_CK_RS282G05A3 | 2 |  | ~
22 | Development Kit | ESP32-DevKitC | U5 | ESP32-DevKitC | ESP32-DevKitC | 1 |  | https://docs.espressif.com/projects/esp-idf/zh_CN/latest/esp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
23 | 5V, 3A SIMPLE SWITCHER® Step-Down Voltage Regulator, TO-263 | LM2576S-5 | U2 | LM2576S-5 | TO-263-5_TabPin3 | 1 |  | http://www.ti.com/lit/ds/symlink/lm2576.pdf | C194472
24 | Voltage Comparator, DIP-8/SOIC-8 | LM311 | U1 | LM311 | SOIC-8_3.9x4.9mm_P1.27mm | 1 |  | http://www.ti.com/lit/ds/symlink/lm311.pdf | C12597
